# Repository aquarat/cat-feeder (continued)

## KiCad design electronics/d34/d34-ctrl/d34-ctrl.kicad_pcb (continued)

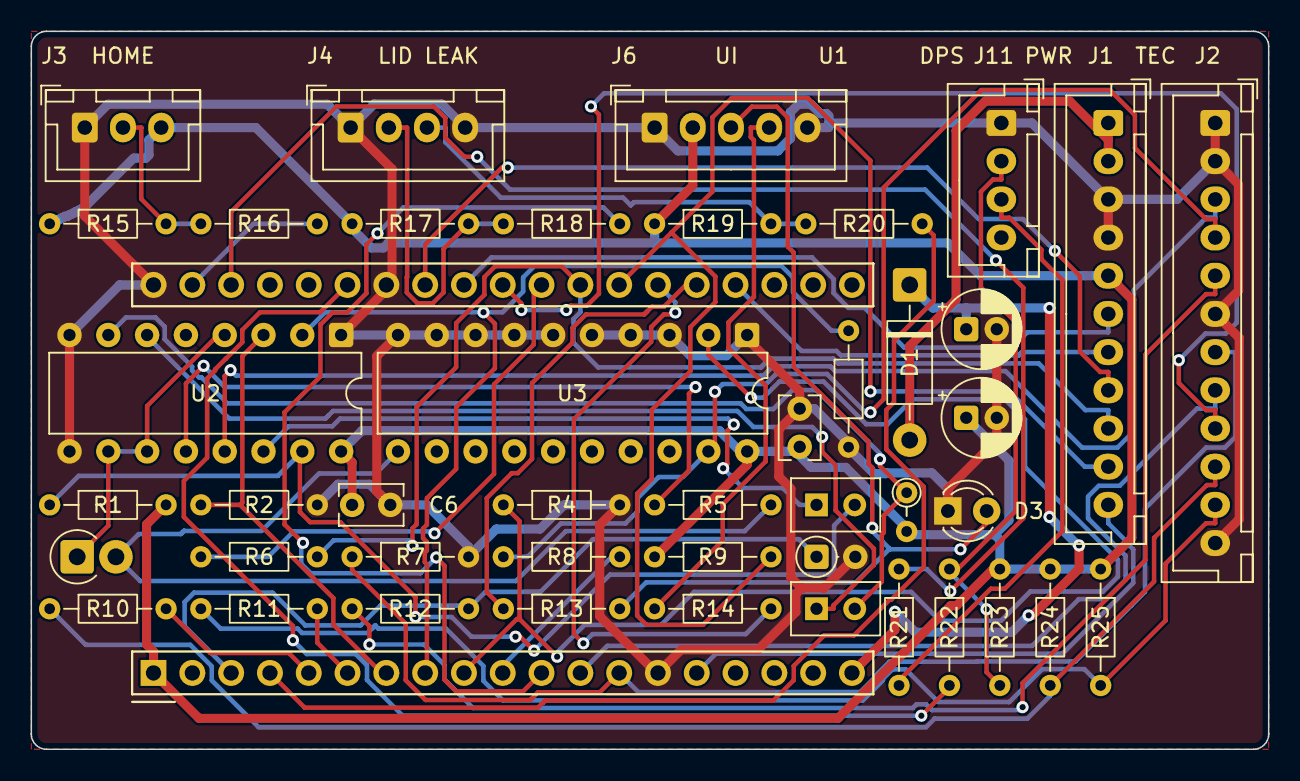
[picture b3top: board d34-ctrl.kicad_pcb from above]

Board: 2 copper layers, 81.0 x 47.0 mm, 45 parts (0 on the bottom side), 47 nets.

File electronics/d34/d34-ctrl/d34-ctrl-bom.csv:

Board,References,Qty,Value,Description,Manufacturer,MPN,KiCad footprint,Supplier,Stock no,Pack,Datasheet,Checked
d34-ctrl,U1,1,,"1x19 2.54 mm socket strip, 8.51 mm (2 per ESP32-DevKitC-32E)",Samtec,SSW-119-01-T-S,d34:ESP32-DevKitC-32E_Socket,RS,207-9240,1,samtec_ssw.pdf; esp32_devkitc_v4_dimensions.pdf,"verified: SSW body 8.51 high, 0.64 sq pins 3.68-6.35 deep; DevKitC rows 25.40, 48.26 x 27.94 + 6.04 antenna (Espressif drawing)"
d34-ctrl,D1 D2,2,,"Schottky 20 V 1 A, DO-41",onsemi,1N5817RLG,Diode_THT:D_DO-41_SOD81_P10.16mm_Horizontal,RS,625-4972,5,1n5817-19.pdf,"verified: VF max 0.32 V @ 0.1 A, 0.45 V @ 1 A; 20 V; DO-41 (onsemi p2)"
d34-ctrl,C1 C2,2,,"22 uF 50 V electrolytic, 5 x 11 mm",Rubycon,50YXF22M5X11,Capacitor_THT:CP_Radial_D5.0mm_P2.00mm,RS,224-4331,5,rubycon_yxf.pdf,"verified: 5 x 11 mm, 150 mA ripple (YXF p2); series marked obsolete by Rubycon but RS stock 1365 (2026-10-26); drop-in: Panasonic EEU-FR1H220 (FR p1, F 2.0 mm)"
d34-ctrl,D3,1,,3 mm green LED,Broadcom,HLMP-1503,LED_THT:LED_D3.0mm,RS,180-8502,10,hlmp-1503.pdf,"verified: D 3.17, H 6.35 max, leads 2.54 nominal, cathode = short lead, hole 0.98-1.08 (p1, p11)"
d34-ctrl,J1,1,,11-pin JST XH shrouded header,JST,B11B-XH-A(LF)(SN),Connector_JST:JST_XH_B11B-XH-A_1x11_P2.50mm_Vertical,RS,820-1535,10,jst_xh.pdf,"verified: eXH pitch 2.5, length 2.5(n-1)+4.9, h 7.0, hole 0.9-1.0, mated 9.8"
d34-ctrl,J2,1,,12-pin JST XH shrouded header,JST,B12B-XH-A(LF)(SN),Connector_JST:JST_XH_B12B-XH-A_1x12_P2.50mm_Vertical,RS,820-1539,10,jst_xh.pdf,"verified: eXH pitch 2.5, length 2.5(n-1)+4.9, h 7.0, hole 0.9-1.0, mated 9.8"
d34-ctrl,J11 J4,2,,4-pin JST XH shrouded header,JST,B4B-XH-A(LF)(SN),Connector_JST:JST_XH_B4B-XH-A_1x04_P2.50mm_Vertical,RS,820-1551,5,jst_xh.pdf,"verified: eXH pitch 2.5, length 2.5(n-1)+4.9, h 7.0, hole 0.9-1.0, mated 9.8"
d34-ctrl,U2,1,,"Dual retriggerable monostable, DIP-16 (TEC watchdog)",Toshiba,TC74HC123AP(F),Package_DIP:DIP-16_W7.62mm,RS,539-9456,5,tc74hc123ap.pdf,"verified: standard 74HC123 pinout, 2-6 V, tw ~= 1.0 Cx Rx (1 uF x 1 M ~ 1.0 s), Rx <= 1 M, DIP-16 4.15+-0.3 high (Toshiba JP sheet p1, p5-p10)"
d34-ctrl,U3,1,,"Octal transparent latch, DIP-20 (defrost-relay interlock)",Texas Instruments,SN74HC573AN,Package_DIP:DIP-20_W7.62mm,RS,217-5667,1,sn74hc573a.pdf,"verified: pinout p3, N20 rows 7.62, 5.08 max (p3, p31)"
d34-ctrl,R1 R26,2,,Resistor 470 k 1 % 0204 (74HC123 timing),Vishay,MBA02040C4703FRP00,Resistor_THT:R_Axial_DIN0204_L3.6mm_D1.6mm_P7.62mm_Horizontal,Farnell,4177865,10,,"Farnell listing: MBA 0204, 470 k, 1 %, 0.4 W (same 0204 body as MF0204; RS has no 470 k 0204 in small packs)"
d34-ctrl,R2 R4 R7 R15 R17 R20 R23 R24 R25,9,10k,"Resistor, metal film MF0204, 0.4 W, 1 %, axial",Yageo,MF0204FTE52-10K,Resistor_THT:R_Axial_DIN0204_L3.6mm_D1.6mm_P7.62mm_Horizontal,RS,199-7794,100,yageo_mf0.pdf,"verified: body 3.4+-0.3 x 1.9+-0.2 mm, lead 0.45 mm, M-forming P 6.0 mm (Yageo MF0 spec p3, p9)"
d34-ctrl,R3 R12 R19,3,47k,"Resistor, metal film MF0204, 0.4 W, 1 %, axial",Yageo,MF0204FTE52-47K,Resistor_THT:R_Axial_DIN0204_L3.6mm_D1.6mm_P7.62mm_Horizontal,RS,199-7828,100,yageo_mf0.pdf,"verified: body 3.4+-0.3 x 1.9+-0.2 mm, lead 0.45 mm, M-forming P 6.0 mm (Yageo MF0 spec p3, p9)"
d34-ctrl,C6 C7,2,100n,100 nF 50 V X7R radial MLCC,Murata,RDER71H104K0P1H03B,Capacitor_THT:C_Rect_L4.0mm_W2.5mm_P2.50mm,RS,190-2933,10,murata_rde.pdf,"verified: size 0 = 4.0 W x 2.5 T x 6.0 H mm, lead 0.5, P1 = 2.5 mm (RDE p2); h incl. coating allowance"
d34-ctrl,R5 R6 R8 R10 R11 R14 R16 R18 R21 R22,10,1k,"Resistor, metal film MF0204, 0.4 W, 1 %, axial",Yageo,MF0204FTE52-1K,Resistor_THT:R_Axial_DIN0204_L3.6mm_D1.6mm_P7.62mm_Horizontal,RS,199-7806,100,yageo_mf0.pdf,"verified: body 3.4+-0.3 x 1.9+-0.2 mm, lead 0.45 mm, M-forming P 6.0 mm (Yageo MF0 spec p3, p9)"
d34-ctrl,R9,1,4.7k,"Resistor, metal film MF0204, 0.4 W, 1 %, axial",Yageo,MF0204FTE52-4K7,Resistor_THT:R_Axial_DIN0204_L3.6mm_D1.6mm_P7.62mm_Horizontal,RS,199-7830,100,yageo_mf0.pdf,"verified: body 3.4+-0.3 x 1.9+-0.2 mm, lead 0.45 mm, M-forming P 6.0 mm (Yageo MF0 spec p3, p9)"
d34-ctrl,D9,1,,"Schottky clamp, DO-35 vertical (IO36 negative clamp)",STMicroelectronics,BAT42,Diode_THT:D_DO-35_SOD27_P2.54mm_Vertical_AnodeUp,RS,544-4758,5,bat42.pdf,"BAT42 small-signal Schottky 30 V, DO-35 (Vishay BAT42 sheet saved; ST part from RS): VF ~0.2-0.3 V at uA-mA"
d34-ctrl,R13,1,330,"Resistor, metal film MF0204, 0.4 W, 1 %, axial",Yageo,MF0204FTE52-330R,Resistor_THT:R_Axial_DIN0204_L3.6mm_D1.6mm_P7.62mm_Horizontal,RS,199-7821,100,yageo_mf0.pdf,"verified: body 3.4+-0.3 x 1.9+-0.2 mm, lead 0.45 mm, M-forming P 6.0 mm (Yageo MF0 spec p3, p9)"
d34-ctrl,C4 C5,2,1u,1 uF 50 V X7R radial MLCC,Murata,RDER71H105K2P1H03B,d34:C_Rect_L5.5mm_W3.2mm_P2.50mm,RS,190-2943,10,murata_rde.pdf,"verified: size 2 = 5.5 W x 3.15 T x 6.0 H mm, lead 0.5, P1 = 2.5 mm (RDE p2); custom footprint to that outline"
d34-ctrl,J3,1,,3-pin JST XH shrouded header,JST,B3B-XH-A(LF)(SN),Connector_JST:JST_XH_B3B-XH-A_1x03_P2.50mm_Vertical,RS,820-1557,5,jst_xh.pdf,"verified: eXH pitch 2.5, length 2.5(n-1)+4.9, h 7.0, hole 0.9-1.0, mated 9.8"
d34-ctrl,J6,1,,5-pin JST XH shrouded header,JST,B5B-XH-A(LF)(SN),Connector_JST:JST_XH_B5B-XH-A_1x05_P2.50mm_Vertical,RS,820-1560,5,jst_xh.pdf,"verified: eXH pitch 2.5, length 2.5(n-1)+4.9, h 7.0, hole 0.9-1.0, mated 9.8"
d34-ctrl,(off-board),1,,ESP32-DevKitC-32E module (plugs into U1 sockets); not stocked by RS/Farnell/CPC,Espressif,ESP32-DevKitC-32E,,Rapid Electronics,09-1099,,esp32_devkitc_v4_dimensions.pdf; esp32_devkitc_v4_sch.pdf,"verified: Espressif drawing + V4 schematic (5V pin after BAT760, AMS1117-3.3); DigiKey UK 1965-ESP32-DEVKITC-32E-ND GBP 7.47 is the alternative"
d34-ctrl,(off-board),1,,JST XH housing 3-way (home sensor lead),JST,XHP-3,,RS,820-1614,5,jst_xh.pdf,
d34-ctrl,(off-board),29,,"JST XH crimp contact SXH-001T-P0.6, AWG 28-22, for the three XH leads longer than any stocked pre-crimped lead: W01 ctrl-pwr link 335 mm (22), W28 lid reed 325 mm (2), W29 panel 300 mm (5); hand crimper Engineer PA-09",JST,SXH-001T-P0.6,,RS,123-5947,250,jst_xh.pdf,
d34-ctrl,(off-board),2,,JST XH housing 4-way (DPS5005 UART lead; lid reed + basin probe SENSE lead),JST,XHP-4,,RS,820-1618,5,jst_xh.pdf,
d34-ctrl,(off-board),1,,JST XH housing 5-way (panel LED/button lead),JST,XHP-5,,RS,820-1627,5,jst_xh.pdf,
d34-ctrl,(off-board),2,,"JST XH housing 11-way (ctrl-pwr link, both ends)",JST,XHP-11,,RS,820-1523,10,jst_xh.pdf,
d34-ctrl,(off-board),2,,"JST XH housing 12-way (ctrl-tec link, both ends)",JST,XHP-12,,RS,820-1532,10,jst_xh.pdf,
d34-ctrl,(off-board),26,,"JST XH pre-crimped lead, 300 mm 26 AWG, SXH contact both ends. W02 ctrl-tec link (12, both ends) and the single-ended leads W12, W30, W31, W33, W34 (14: each lead cut near ONE end, ~290 mm usable)",JST,01SXHSXH-26L300,,RS,820-1541,10,jst_xh.pdf,retailer data (RS/Farnell listing); contact = SXH-001T-P0.6 per eXH

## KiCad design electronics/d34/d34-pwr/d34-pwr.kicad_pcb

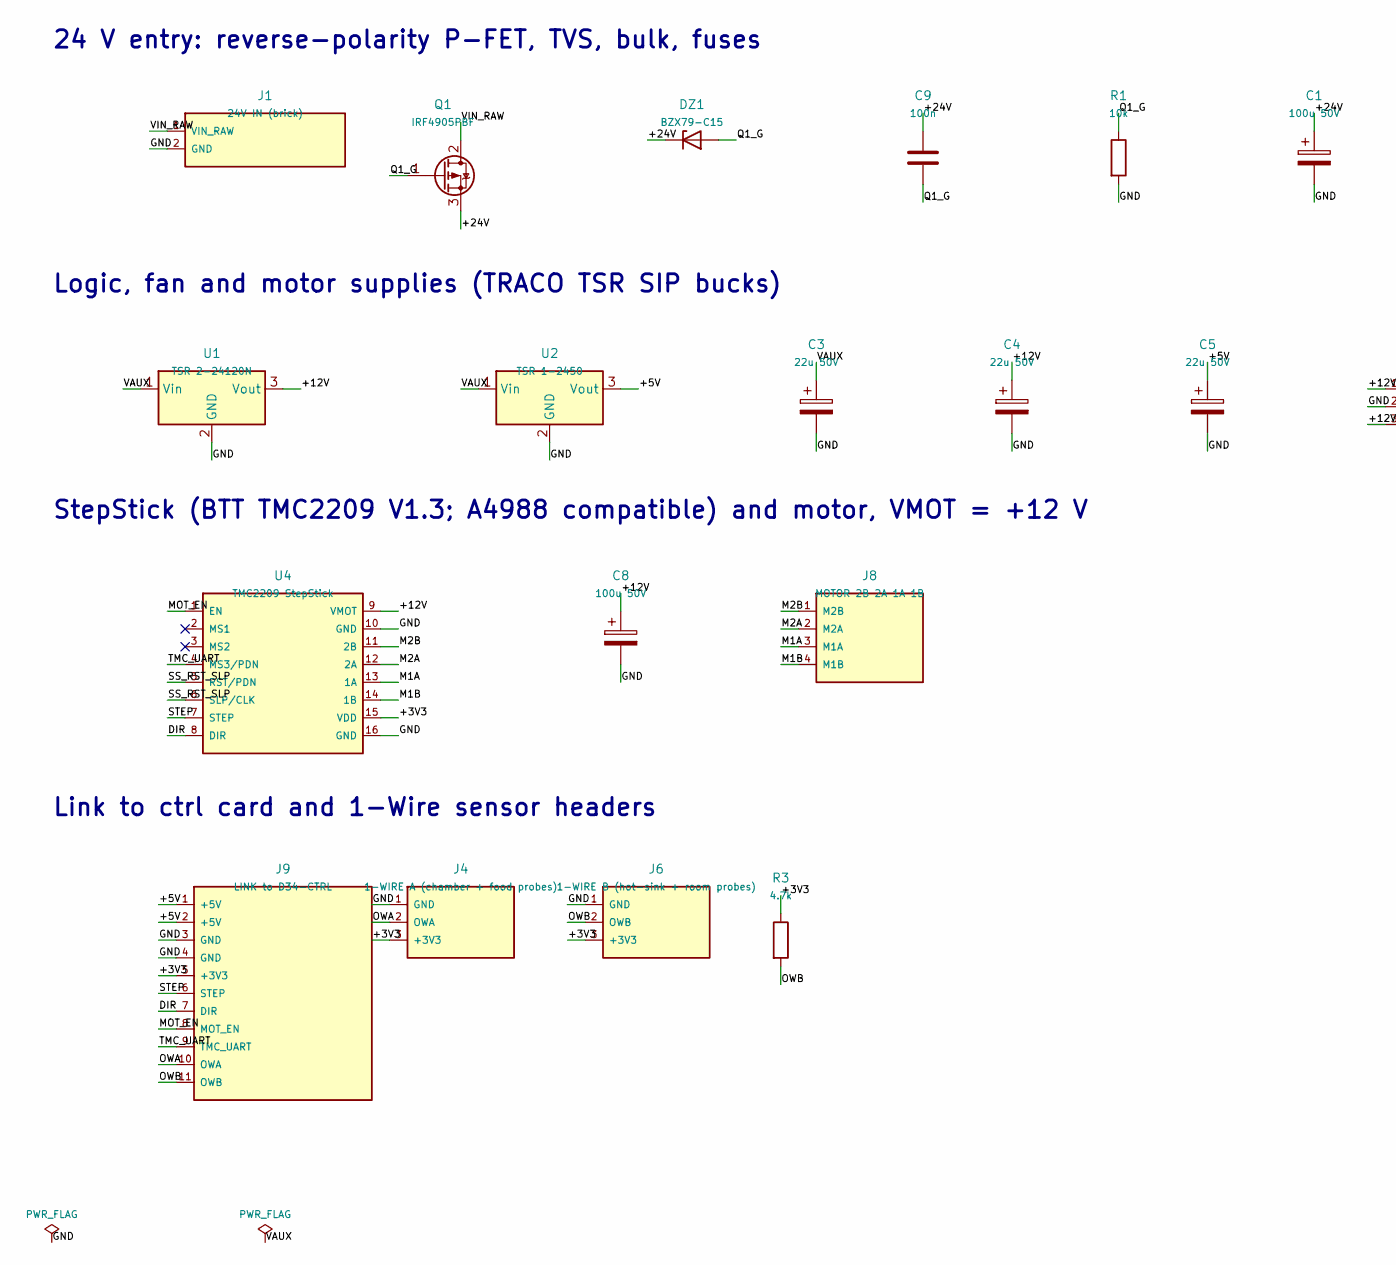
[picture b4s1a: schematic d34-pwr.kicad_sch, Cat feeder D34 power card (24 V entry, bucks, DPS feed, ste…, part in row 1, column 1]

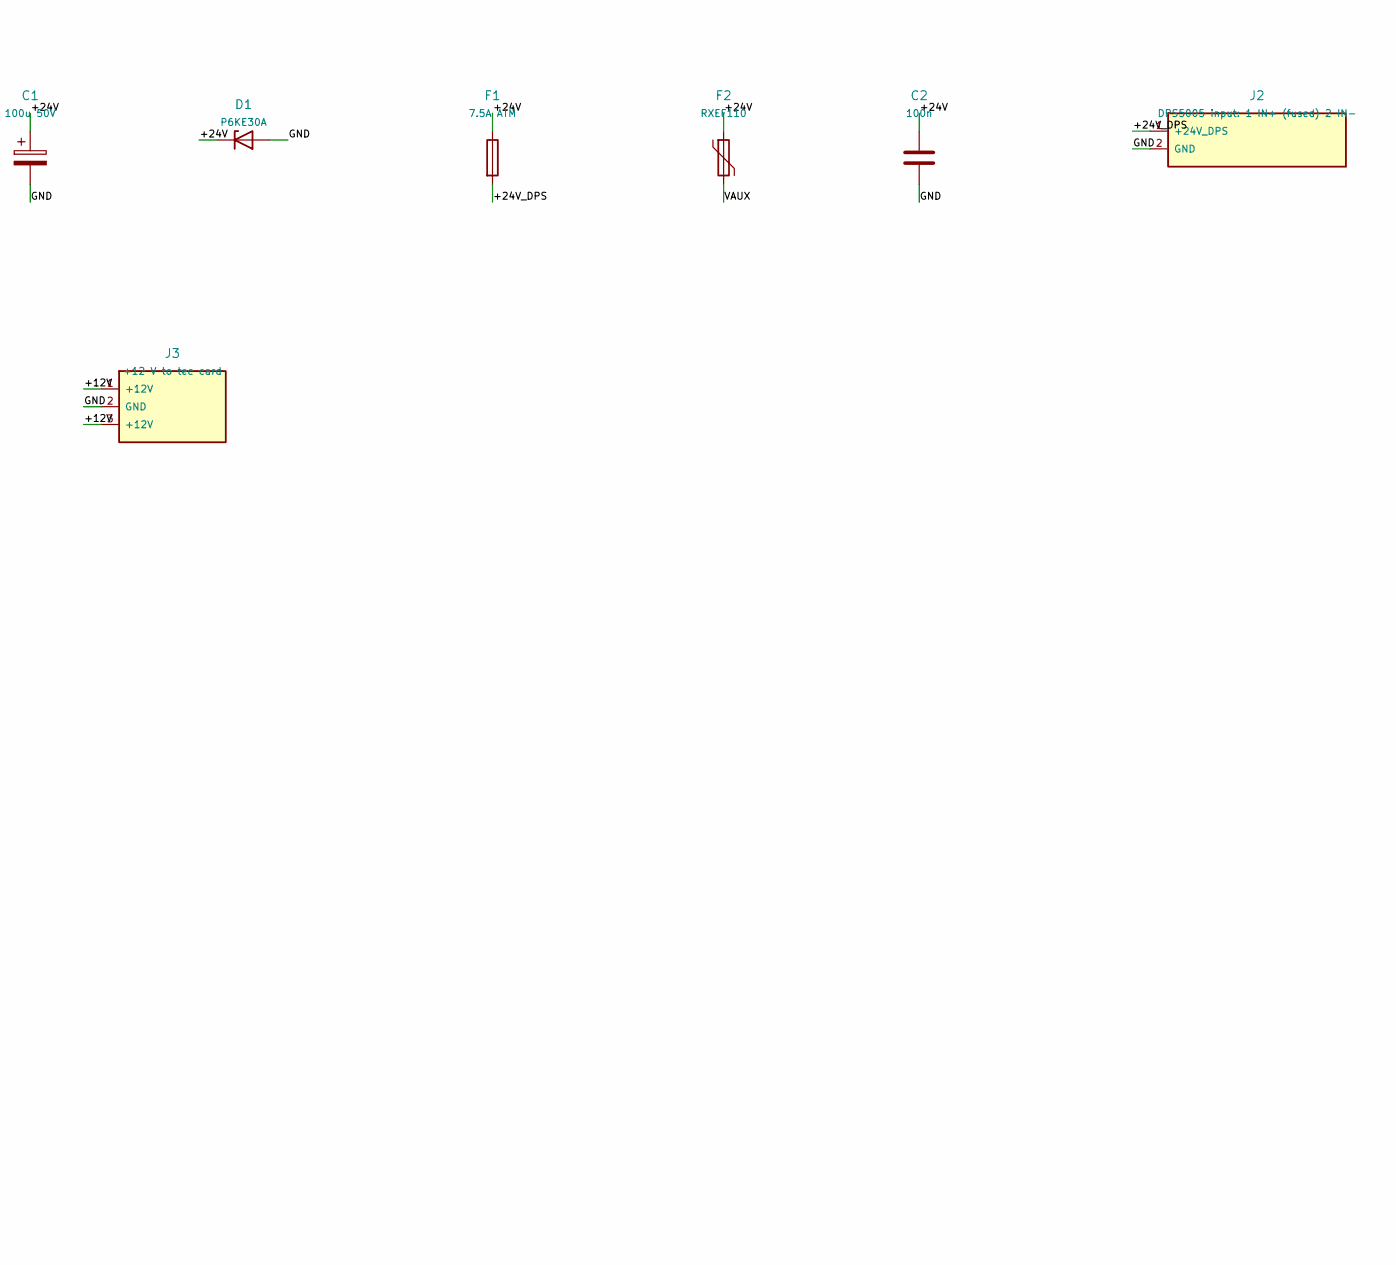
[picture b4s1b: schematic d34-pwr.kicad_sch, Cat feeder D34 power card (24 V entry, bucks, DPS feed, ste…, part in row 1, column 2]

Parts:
C1, C8: 100u 50V; CP_Radial_D8.0mm_P3.50mm; MPN EEU-FR1H101
C2, C9: 100n; C_Rect_L4.0mm_W2.5mm_P2.50mm; MPN RDER71H104K0P1H03B
C3, C4, C5: 22u 50V; CP_Radial_D5.0mm_P2.00mm; MPN 50YXF22M5X11
D1: P6KE30A; D_DO-15_P12.70mm_Horizontal; MPN P6KE30A
DZ1: BZX79-C15; D_DO-35_SOD27_P7.62mm_Horizontal; MPN BZX79-C15,133
F1: 7.5A ATM; Fuseholder_Blade_Mini_Keystone_3568; MPN 3568
F2: RXEF110; PTC_Radial_L13.0mm_W3.2mm_P5.08mm; MPN RXEF110
J1: 24V IN (brick); Molex_Mini-Fit_Jr_5566-02A_2x01_P4.20mm_Vertical; MPN 39-28-1023 (5566-02A)
J2: DPS5005 input: 1 IN+ (fused) 2 IN-; PhoenixContact_MSTBVA_2,5_2-G-5,08_1x02_P5.08mm_Vertical; MPN MSTBVA 2,5/2-G-5,08 (1755736)
J3: +12 V to tec card; JST_VH_B3P-VH_1x03_P3.96mm_Vertical; MPN B3P-VH(LF)(SN)
J4: 1-WIRE A (chamber + food probes); JST_XH_B3B-XH-A_1x03_P2.50mm_Vertical; MPN B3B-XH-A(LF)(SN)
J6: 1-WIRE B (hot-sink + room probes); JST_XH_B3B-XH-A_1x03_P2.50mm_Vertical; MPN B3B-XH-A(LF)(SN)
J8: MOTOR 2B 2A 1A 1B; JST_VH_B4P-VH_1x04_P3.96mm_Vertical; MPN B4P-VH(LF)(SN)
J9: LINK to D34-CTRL; JST_XH_B11B-XH-A_1x11_P2.50mm_Vertical; MPN B11B-XH-A(LF)(SN)
Q1: IRF4905PBF; TO-220-3_Vertical; MPN IRF4905PBF
R1: 10k; R_Axial_DIN0204_L3.6mm_D1.6mm_P7.62mm_Horizontal; MPN MF0204FTE52-10K
R3: 4.7k; R_Axial_DIN0204_L3.6mm_D1.6mm_P7.62mm_Horizontal; MPN MF0204FTE52-4K7
U1: TSR 2-24120N; Converter_DCDC_TRACO_TSR2-24xxN_TSR2-24xxxN_THT; MPN TSR 2-24120N
U2: TSR 1-2450; Converter_DCDC_TRACO_TSR-1_THT; MPN TSR 1-2450
U4: TMC2209 StepStick; StepStick_Socket_2x8_W12.70mm; MPN SSW-108-01-T-S

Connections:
/+3V3: J4.3 (+3V3), J6.3 (+3V3), J9.5 (+3V3), R3.1, U4.15 (VDD)
/+5V: C5.1, J9.1 (+5V), J9.2 (+5V), U2.3 (Vout)
/+12V: C4.1, C8.1, J3.1 (+12V), J3.3 (+12V), U1.3 (Vout), U4.9 (VMOT)
/+24V: C1.1, C2.1, C9.1, D1.1 (K), DZ1.1 (K), F1.1, F2.1, Q1.3 (S)
/+24V_DPS: F1.2, J2.1 (+24V_DPS)
/DIR: J9.7 (DIR), U4.8 (DIR)
/GND: C1.2, C2.2, C3.2, C4.2, C5.2, C8.2, D1.2 (A), J1.2 (GND), J2.2 (GND), J3.2 (GND), J4.1 (GND), J6.1 (GND), J9.3 (GND), J9.4 (GND), R1.2, U1.2 (GND), U2.2 (GND), U4.10 (GND), U4.16 (GND)
/M1A: J8.3 (M1A), U4.13 (1A)
/M1B: J8.4 (M1B), U4.14 (1B)
/M2A: J8.2 (M2A), U4.12 (2A)
/M2B: J8.1 (M2B), U4.11 (2B)
/MOT_EN: J9.8 (MOT_EN), U4.1 (EN)
/OWA: J4.2 (OWA), J9.10 (OWA)
/OWB: J6.2 (OWB), J9.11 (OWB), R3.2
/Q1_G: C9.2, DZ1.2 (A), Q1.1 (G), R1.1
/SS_RST_SLP: U4.5 (RST/PDN), U4.6 (SLP/CLK)
/STEP: J9.6 (STEP), U4.7 (STEP)
/TMC_UART: J9.9 (TMC_UART), U4.4 (MS3/PDN)
/VAUX: C3.1, F2.2, U1.1 (Vin), U2.1 (Vin)
/VIN_RAW: J1.1 (VIN_RAW), Q1.2 (D)

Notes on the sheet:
24 V entry: reverse-polarity P-FET, TVS, bulk, fuses
Logic, fan and motor supplies (TRACO TSR SIP bucks)
StepStick (BTT TMC2209 V1.3; A4988 compatible) and motor, VMOT = +12 V
Link to ctrl card and 1-Wire sensor headers

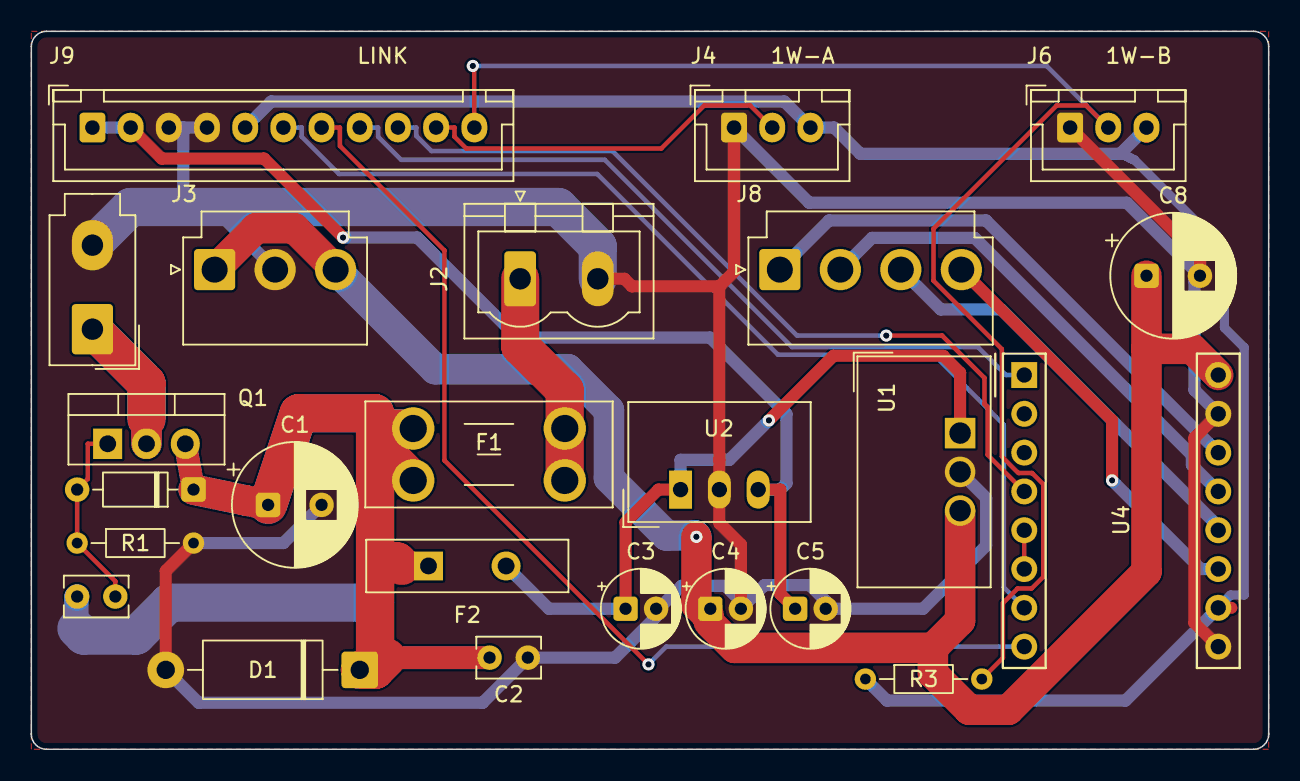
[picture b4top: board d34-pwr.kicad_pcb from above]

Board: 2 copper layers, 81.0 x 47.0 mm, 24 parts (0 on the bottom side), 20 nets.

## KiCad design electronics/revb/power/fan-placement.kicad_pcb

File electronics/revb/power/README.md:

# Rev B power-block handoff

**Selected:** AP63203WU-7 / C780769 for 3.3 V (1 A design budget); AP63201WU-7 / C2071044 for approximately 12 V (0.5 A fan-start budget, 0.14 A normal).

Read [rationale, layout constraints and qualification gaps](../../../kb/pcb-buck-integration.md).

- `circuit.json`: complete **22-component** numbered-pin integration contract, MPNs, JLC codes, KiCad symbols/footprints, datasheet links.
- `design.py`: source generator; follows the motor block's parts schema.
- `analysis.json`, `analyze.py`, `test_power.py`: explicit assumptions and eight analytical/fault-injection tests.
- `stock-evidence.json`, `refresh-stock.py`: read-only public stock snapshots, including rejected candidates; selection is defined by `circuit.json`, not by presence in the evidence file.
- `kicad-audit.json`, `audit_kicad.py`, `power.pretty/`: installed KiCad 9.0.2 symbol/pad checks and exact standard footprint copies.
- `reference-sources.json`, retained PDFs/text: manufacturer-authored reference evidence and mirror provenance.

**Required upstream contract:** `SYS_20V` is a hardware-qualified 20 V switched supply, OFF for fallback contracts and contract loss. Both buck EN pins tie to this supply. Neither rail waits on ESP32 firmware. Feed motor power and DPS5005 separately from the qualified 20 V bus; include the buck banks' 40 µF nominal input capacitance in upstream switch inrush calculations.

The new PCB integrator must check layout/loop/transient/thermal behavior. These files contain no full-board layout and no physical test results. Capacitor DC-bias retention and 10 µs load-step recovery are screening assumptions, not measured guarantees. The 0.5 A fan-start budget is not a qualified continuous thermal rating.

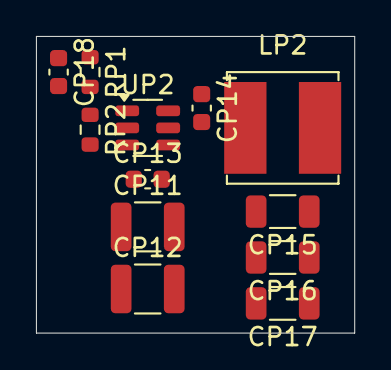
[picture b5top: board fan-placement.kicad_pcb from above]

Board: 2 copper layers, 17.7 x 16.5 mm, 12 parts (0 on the bottom side), 6 nets, no tracks yet.

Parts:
CP11, CP12: 10u 50V X7R; C_1210_3225Metric
CP13, CP14: 100n 50V X7R; C_0603_1608Metric
CP15, CP16, CP17: 22u 25V X5R; C_1206_3216Metric
CP18: 56p 50V C0G; C_0603_1608Metric
LP2: 10uH; L_Bourns_SRN6045TA
RP1: 249k 1%; R_0603_1608Metric
RP2: 18k 1%; R_0603_1608Metric
UP2: AP63201WU-7; TSOT-23-6

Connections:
+12V: CP15.1, CP16.1, CP17.1, CP18.1, LP2.2, RP1.1
GND: CP11.2, CP12.2, CP13.2, CP15.2, CP16.2, CP17.2, RP2.2, UP2.4
PWR_BST2: CP14.1, UP2.6
PWR_FB12: CP18.2, RP1.2, RP2.1, UP2.1
PWR_SW2: CP14.2, LP2.1, UP2.5
SYS_20V: CP11.1, CP12.1, CP13.1, UP2.2, UP2.3

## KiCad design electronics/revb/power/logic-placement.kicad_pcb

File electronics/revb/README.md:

# Controller revision B — integrated power and motion

**In development.** The owner requested integrating USB-C PD, the stepper
driver and the logic/fan regulators onto the main PCB. This revision is a new
design, not the independently reviewed revision A saved in the supplier project.

## Intended electrical architecture

```text
USB-C, 20 V / 5 A capable source and e-marked cable
  └─ STUSB4500 negotiation, protection and controlled power path
       ├─ efficient 3.3 V supply → ESP32, sensors and interface logic
       ├─ efficient 12 V supply → four-wire fan
       ├─ onboard current-regulating A4988 → bipolar stepper
       └─ DC power output → external DPS5005 → TEC array
```

The PD breakout, plug-in motor carrier and separate logic/fan buck modules are
replaced by assembler-fitted components. The DPS5005 remains a separate TEC
regulator. A 100 W input contract is a total-source budget, not 100 W available
to the TECs after auxiliaries and conversion losses.

Functional circuit selection, component stock/footprint checks and JLCPCB
design-rule research are being developed in `pd/`, `motor/`, `power/` and `dfm/`.
The generator emits an editable KiCad schematic and explicitly **unrouted**
placement; those alone are not manufacturing deliverables. Routing, DRC,
electrical review, populated enclosure clearance and supplier-process checks
must refer to this revision's actual artifacts.

## Version identification

`version.py` computes a full SHA-256 digest of the explicitly listed circuit,
footprint and layout sources. The PCB silkscreen and schematic title carry:

- `Rev B / <12-character Git hash>` for committed, unchanged design sources;
- the same with `-dirty` when those sources differ or are untracked;
- `Rev B / src-<12-character source hash>` before the first Git commit.

`version.json` records the full commit, source digest and individual source
hashes. Generated PCB/Gerber/BOM files are hashed separately after export;
feeding them into their own printed identifier would create a circular hash.
The Git identifier is the latest commit touching the listed design sources;
committing only generated artifacts therefore does not force another identifier.
The current repository has no commits, so its initial identifier uses the
source hash. No commit or supplier upload is implicit in generating a version.

Revision A's frozen files and simulation results remain under `../pcb/` and
`../sim/`. Their numerical checks do not qualify the changed revision B circuit.

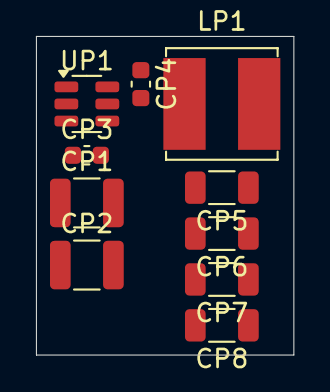
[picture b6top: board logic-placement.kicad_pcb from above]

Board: 2 copper layers, 14.3 x 17.7 mm, 10 parts (0 on the bottom side), 5 nets, no tracks yet.

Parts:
CP1, CP2: 10u 50V X7R; C_1210_3225Metric
CP3, CP4: 100n 50V X7R; C_0603_1608Metric
CP5, CP6, CP7, CP8: 22u 25V X5R; C_1206_3216Metric
LP1: 6.8uH; L_Bourns_SRN6045TA
UP1: AP63203WU-7; TSOT-23-6

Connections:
+3V3: CP5.1, CP6.1, CP7.1, CP8.1, LP1.2, UP1.1
GND: CP1.2, CP2.2, CP3.2, CP5.2, CP6.2, CP7.2, CP8.2, UP1.4
PWR_BST1: CP4.1, UP1.6
PWR_SW1: CP4.2, LP1.1, UP1.5
SYS_20V: CP1.1, CP2.1, CP3.1, UP1.2, UP1.3

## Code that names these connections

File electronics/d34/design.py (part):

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# signals whose boot level is safe: IO0 button (pull-up on DevKit), IO2 LED
# (pull-down via LED), IO12 fan PWM with 10k pull-down (3.3 V flash), IO5 fan PWM,
# IO15 DIR (no external pull). TEC_EN/WDT_KICK use IO32/IO33, quiet at reset.
GPIO = {'3V3': '+3V3', 'EN': None, 'IO36': 'THERMO_OK_IN', 'IO39': 'LEAK_IN', 'IO34': 'TACH1_IN', 'IO35': 'TACH2_IN',
        'IO32': 'TEC_EN', 'IO33': 'WDT_KICK', 'IO25': 'DEFROST_REQ', 'IO26': 'DEFROST_FB', 'IO27': 'LID_IN',
        'IO14': 'FAN2_PWM', 'IO12': 'FAN1_PWM', 'GND': 'GND', 'IO13': 'OWB', 'SD2': None, 'SD3': None,
        'CMD': None, '5V': '+5V_DK',
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    B.conn('J1', 'XH11', 'LINK to D34-PWR', LINK_PWR, 70.5, 6.0, 270, label='LINK-PWR', ref_at=(70.0, 1.6, 0))
    B.conn('J2', 'XH12', 'LINK to D34-TEC', LINK_TEC, 77.5, 6.0, 270, label='LINK-TEC', ref_at=(77.0, 1.6, 0))
    B.conn('J11', 'XH4', 'DPS5005 UART (3.3 V TTL; DPS order GND TX RX 3V3)',
           [('GND', 'GND'), ('DPS_TXD', 'LOGIC'), ('DPS_RXD', 'LOGIC'), (None, 'NC')], 63.5, 6.0, 270, label='DPS', ref_at=(63.0, 1.6, 0))
    # ---------------------------------------------------------- safety logic (under the DevKit)
    B.group = 'TEC watchdog (74HC123) and defrost interlock latch (74HC573)'
    # Both DIPs are turned 270 deg so VCC (pin 16 / pin 20) sits at the bottom-right corner, next to its
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          note='holds LE low (<= 0.4 V) whenever 1Q-bar is low, i.e. while K1 is commanded on')
    B.add('R26', 'R470V', '470k', {1: 'LD_RC', 2: '+3V3'}, 57.3, 30.2, 270, ref_at='hide', note='latch-delay timing (74HC123 half 2)')
    ur('R6', '1k', 'TMC_TX_G', 'TMC_UART', 1, 1, note='TMC2209 single-wire UART: TX via 1k, RX (IO16) direct')
    ur('R7', '10k', 'FAN1_PWM', 'GND', 2, 1, note='GPIO12 strap must read low at boot (3.3 V flash)')
    ur('R8', '1k', 'K2_ON', 'DEFROST_FB', 3, 1, note='latched K2 state read back on IO26')
    ur('R9', '4.7k', '+3V3', 'OWA', 4, 1, note='1-Wire bus A pull-up (bus B pull-up is on the pwr card)')
    ur('R10', '1k', 'TACH1', 'TACH1_IN', 0, 2)
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    s3 = [('GND', 'GND'), ('HOME', 'LOGIC'), ('+3V3', '3V3')]
    # Harness-access pass (2026-10-26): three plugs instead of four, spread to ~7 mm gaps. The lid reed and the
    # basin-full probe arrive on two cables that terminate in the same XHP-4 housing (J4 = GND, LID, LEAK, GND).
    B.conn('J3', 'XH3', 'HOME sensor (DRV5023 hall, 3.3 V, open drain)', s3, 3.5, 6.3, 0, label='HOME', ref_at=(1.5, 1.6, 0))
    B.conn('J4', 'XH4', 'LID reed + basin-full probe', [('GND', 'GND'), ('LID', 'LOGIC'), ('LEAK', 'ANALOG'), ('GND', 'GND')],
           20.9, 6.3, 0, label='SENSE', ref_at=(18.9, 1.6, 0))
    B.conn('J6', 'XH5', 'UI: panel LED + button', [('GND', 'GND'), ('+3V3', '3V3'), ('LED_EXT', 'LOGIC'), ('BTN', 'LOGIC'), ('GND', 'GND')],
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                    'Motor': dict(width=0.8, clearance=0.3, nets=['M1A', 'M1B', 'M2A', 'M2B'])}
    B.solid_pads = set(HC)
    B.group = '24 V entry: reverse-polarity P-FET, TVS, bulk, fuses'
    # J1 is turned 180 deg (pin 1 = +24 V at the bottom) so VIN_RAW runs 8 mm to the FET drain on both
    # layers without crossing the brick return; GND leaves upwards and runs above the VH/MSTB row.
    B.conn('J1', 'MF2', '24V IN (brick)', [('VIN_RAW', '24V'), ('GND', 'GND')], 4.0, 19.5, 180, label='24V IN', ref_at='hide')
    B.add('Q1', 'IRF4905', 'IRF4905PBF', {1: 'Q1_G', 2: 'VIN_RAW', 3: '+24V'}, 5.0, 27.0, 0, ref_at=(14.5, 24.0, 0),
          note='conducts only with correct input polarity; gate clamped to -15 V')
    B.add('DZ1', 'DZ15S', 'BZX79-C15', {1: '+24V', 2: 'Q1_G'}, 10.62, 30.0, 180, ref_at='hide')
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    B.add('F3', 'PTC050', 'RXEF050', {1: '+12V', 2: 'FAN3_12'}, 61.2, 20.0, 0, ref_at='hide', note='FAN3 (spare) feed')
    B.add('Q4', 'IRLZ44N', 'IRLZ44N', {1: 'FAN2_PWM', 2: 'FAN2_N', 3: 'GND'}, 62.0, 26.9, 0, ref_at='hide', note='FAN2 low side')
    B.add('Q5', 'IRLZ44N', 'IRLZ44N', {1: 'FAN3_PWM', 2: 'FAN3_N', 3: 'GND'}, 72.7, 26.9, 0, ref_at='hide', note='FAN3 low side')
    B.conn('J5', 'FAN4', 'FAN1 12 V 4-pin PWM (NF-A12x25)', [('GND', 'GND'), ('FAN1_12', '12V'), ('TACH1', 'LOGIC'), ('FAN1_OD', 'LOGIC')],
           37.0, 6.4, 0, label='FAN1', ref_at=(35.0, 1.6, 0))
    B.conn('J6', 'FAN4', 'FAN2 12 V blower (switched DC low side), tach', [('FAN2_N', 'FANGND'), ('FAN2_12', '12V'), ('TACH2', 'LOGIC'), (None, 'NC')],
           48.5, 6.4, 0, label='FAN2', ref_at=(46.5, 1.6, 0))
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
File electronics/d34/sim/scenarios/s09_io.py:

"""S09 - Sensor and I/O interfaces (ngspice, full system powered).

1-Wire rise time on both buses with all probe leads at maximum length; lid / home / leak input levels through
their series resistors and leads; ESD into a lid lead (HBM and IEC 61000-4-2 contact) vs the ESP32 pin clamps;
ESP32 strapping pin levels at reset; THERMO_OK and DEFROST_FB logic levels.
"""
import numpy as np

from d34sim import common, flows, report
from d34sim import models as M_
from d34sim.circuit import Ctx
from d34sim.netlist import spice_node

TITLE = '1-Wire timing, digital input levels, ESD into leads, ESP32 strapping pins'


def run(env):
    chk = report.Checks('s09_io', env.outdir('s09_io'))
    L = env.limit
    N, R = flows.names(env)
    ctrl = env.cards['ctrl']
    dk = R['devkit']
    io = {ctrl.pin_func[(dk, p)]: net for p, net in ctrl.pins(dk).items()}
    nio = lambda gpio: spice_node('ctrl', io[gpio]).lower()
    vdd = 3.3
    vih, s_vih = L('esp32_vih_frac')
    vil, s_vil = L('esp32_vil_frac')
    # ------------------------------------------------------------------ 1-Wire
    ow_leads = [k for k, v in env.harness['leads'].items() if v['b'] == 'ext:ds18b20' and env.cards['pwr'].pins(v['a'][1])]
    onewire = {k: dict(pull='DC 0', c_in=25e-12) for k in ow_leads}
    first = {}
    for k in ow_leads:   # one sensor per bus pulls low 100-110 us, then releases
        net = env.cards['pwr'].net(env.harness['leads'][k]['a'][1], '2')
        if net not in first:
            first[net] = k
            onewire[k]['pull'] = 'PWL(0 0 100u 0 100.02u 1 110u 1 110.02u 0)'
    rows = []
    for corner in ('nom', 'max'):
        def make(nv):
            ctx = Ctx(dict(temp_C=40.0, length=corner, C=corner), no_vendor=nv)
            return common.build(env, ctx, brick=dict(v=24.0, t_close=None), onewire=onewire)
        bus_gpio = {net: [g for g, n in io.items() if n == net] for net in first}
        vecs = [f'v({nio(g[0])})' for g in bus_gpio.values() if g]
        c, info, r = common.run_robust(make, f's09_ow_{corner}', vecs, 'tran 20n 140u 0 50n', chk)
        t = r['time']
        for (net, g), v in zip(bus_gpio.items(), vecs):
            t_ds = common.first_cross(t, r[v], L('ds18b20_vih')[0], after=110e-6) - 110e-6
            t_esp = common.first_cross(t, r[v], vih * vdd, after=110e-6) - 110e-6
            vol = r[v][(t > 105e-6) & (t < 109e-6)].mean()
            rows.append(dict(bus=net, gpio=g[0], corner=corner, rise_to_ds_vih_us=t_ds * 1e6, rise_to_esp_vih_us=t_esp * 1e6, vol=vol,
                             probes=sum(env.harness['leads'][k].get('probes', 1) for k in ow_leads
                                        if env.cards['pwr'].net(env.harness['leads'][k]['a'][1], '2') == net)))
    chk.csv('onewire.csv', rows)
    w = max(rows, key=lambda x: x['rise_to_esp_vih_us'])
    s_t = L('onewire_sample_us')
    chk.add('ow_rise', '1-Wire release to ESP32 VIH (0.75 VDD), worst bus, all probe leads 0.5 m', w['rise_to_esp_vih_us'], s_t[0] - 2.0, '<=', 'us',
            f'{s_t[1]}; master releases ~2 us after slot start', corner=f"{w['bus']} ({w['probes']} probes, lead {w['corner']})", severity='functional')
    w = max(rows, key=lambda x: x['vol'])
    chk.add('ow_vol', '1-Wire low level while a DS18B20 pulls down (vs ESP32 VIL)', w['vol'], vil * vdd, '<=', 'V', s_vil, severity='functional')
    # ------------------------------------------------------------------ inputs, strapping, status levels (DC)
    def make_dc(nv):
        ctx = Ctx(dict(temp_C=40.0), no_vendor=nv, boot_pulls=True)
        leads = [k for k in ('LID', 'HOME', 'LEAK') if k in env.harness['leads']]
        c, info = common.build(env, ctx, brick=dict(v=24.0, t_close=None), extra_leads=leads)
        lid, home, leak = (info[k][0] if k in info else {} for k in ('LID', 'HOME', 'LEAK'))
        c.add('* lid switch closed (0.1 ohm + lead), home sensor open collector on (VOL ~0.2 V @ 0.33 mA), leak probe 47 kohm (wet)')
        if lid:
            c.add(f'Rlid {lid["1"]} {lid["2"]} 0.1')
        if home:
            c.add(f'Rhome {home["2"]} home_x 400', f'Vhome home_x {home["1"]} 0.07')
        if leak:
            c.add(f'Rleak {leak["1"]} {leak["2"]} 47k')
        elif lid and '3' in lid and '4' in lid:   # D34-2: basin-full probe shares the lid XH-4 (pins 3/4)
            c.add(f'Rleak {lid["3"]} {lid["4"]} 47k')
        return c, info
    want = ['IO27', 'IO23', 'IO39', 'IO0', 'IO2', 'IO12', 'IO15', 'IO5', 'IO36', 'IO26']
    vecs = [f'v({nio(g)})' for g in want if g in io] + [f'v({N["v3v3"]})']
    c, info, r = common.run_robust(make_dc, 's09_dc', vecs, 'tran 1u 2m 0 10u', chk)
    V = {g: float(r[f'v({nio(g)})'][-1]) for g in want if g in io}
    v33 = float(r[f'v({N["v3v3"]})'][-1])
    chk.add('lid_closed', f'Lid switch closed: level at the ESP32 pin ({io.get("IO27")})', V.get('IO27', np.nan), vil * v33, '<=', 'V', s_vil)
    chk.add('home_on', 'Home sensor active (open collector 0.2 V): level at the ESP32 pin', V.get('IO23', np.nan), vil * v33, '<=', 'V', s_vil)
    chk.add('strap_io12', 'Strapping: GPIO12 (MTDI) at reset must read 0 for 3.3 V flash (WROOM-32E)', V.get('IO12', np.nan), vil * v33, '<=', 'V',
            'ESP32 datasheet strapping: MTDI = 0 -> VDD_SDIO 3.3 V; ' + s_vil, severity='functional')
    chk.add('strap_io0', 'Strapping: GPIO0 at reset reads 1 (SPI boot) with the panel button released', V.get('IO0', np.nan), vih * v33, '>=', 'V',
            s_vih, severity='functional')
    chk.note('Strap levels at reset: ' + ', '.join(f'{g} {V[g]:.2f} V' for g in ('IO0', 'IO2', 'IO5', 'IO12', 'IO15') if g in V) +
             '. GPIO5/GPIO15 only set SDIO timing / boot-log; GPIO2 is don\'t-care when GPIO0 = 1.')
    leak_net = io.get('IO39')
    rpu = [M_.parse_value(ctrl.comps[r]['value']) for r in ctrl.comps if r.startswith('R')
           for nets in [set(ctrl.pins(r).values())] if 'LEAK' in nets and N['v3v3'] and any(x.upper() == '+3V3' for x in nets)]
    rpu = rpu[0] if rpu else 100e3
    leak_rows = [dict(probe_ohm=rp, adc_V=3.3 * rp / (rpu + rp), pullup_ohm=rpu) for rp in (1e3, 10e3, 47e3, 100e3, 470e3, 1e6, 1e9)]
    chk.csv('leak_divider.csv', leak_rows)
    chk.note(f"Basin-full probe (ADC, {rpu / 1e3:.0f} k pull-up): 47 k wet -> {V.get('IO39', float('nan')):.2f} V simulated; dry -> 3.3 V. "
             'Divider table in leak_divider.csv.')
    # ------------------------------------------------------------------ ESD into an input lead (analytic)
    # A discharge into a lead reaches the ESP32 pin through the 1 k series resistor and the pin's clamp diodes; with no
    # TVS the peak pin current is bounded by V_esd / (R_gun + R_series). (A SPICE transient was not used: the pin
    # clamp and rail impedances of the ESP32 at ns time scales are not modelled credibly.)
    r_ser = [M_.parse_value(ctrl.comps[x]['value']) for x in ctrl.comps
             if x.startswith('R') and io.get('IO27') in ctrl.pins(x).values() and 'LID' in ctrl.pins(x).values()]
    r_ser = r_ser[0] if r_ser else 1e3
    esd_rows = []
    for name, (vesd, cesd, resd) in {'HBM 2 kV': (2000, 100e-12, 1500), 'IEC 61000-4-2 2 kV contact': (2000, 150e-12, 330),
                                     'IEC 61000-4-2 8 kV contact': (8000, 150e-12, 330)}.items():
        esd_rows.append(dict(event=name, i_pin_pk_est=vesd / (resd + r_ser), r_series=r_ser))
    chk.csv('esd.csv', esd_rows)
    lim, s = L('esp32_hbm_pin_current')
    hbm = esd_rows[0]
    chk.add('esd_hbm', 'HBM 2 kV on a lid lead: peak current into the ESP32 pin clamp (through the 1 k series resistor)', hbm['i_pin_pk_est'], lim, '<=',
            'A', s, severity='rating', detail='analytic bound V/(R_gun + R_series)')
    for row in esd_rows[1:]:
        chk.add(f"esd_iec_{row['event'].split()[-3]}", f"{row['event']} on a lid lead: peak current into the ESP32 pin clamp", row['i_pin_pk_est'], lim, '<=', 'A',
                s + '; no TVS on the inputs', severity='rating', advisory=True,
                detail='leads are inside the enclosure; exposure is only during servicing. Add a TVS array (e.g. per-input 5 V TVS) if leads are touchable')
    # ------------------------------------------------------------------ status levels
    th = V.get('IO36', np.nan)
    chk.add('thermo_ok_level', 'THERMO_OK (thermostats closed) at the ESP32 input vs VIH (digital read)', th, vih * v33, '>=', 'V', s_vih,
            severity='functional', detail='margin is small; reading IO36 with the ADC (threshold ~1.4 V) avoids it (see S11 Monte Carlo)')
    return chk

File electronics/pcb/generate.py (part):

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# Espressif module pin numbers, not bare-chip pad numbers.
add('U1','ESP32-WROOM-32E-N4','RF_Module:ESP32-WROOM-32E','RF_Module:ESP32-WROOM-32E',{
 1:'GND',2:'+3V3',3:'EN',6:'FAN_TACH',7:'BUS_SENSE',8:'INDEX',9:'HOME',
 10:'TEC_EN',11:'FAN_PWM_GPIO',12:'ONEWIRE',15:'GND',16:'UART_OEn',
 25:'BOOT',27:'DPS_RX',28:'DPS_TX',30:'STEP',31:'DIR',33:'I2C_SDA',
 34:'U0RX',35:'U0TX',36:'I2C_SCL',37:'MOTOR_RUN',38:'GND',39:'GND'},
 (75,63,0),'C701341')
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resistor(5,'10k','+3V3','HOME',63,83)
resistor(6,'10k','+3V3','TACH_EXT',88,73)
resistor(7,'1k','TACH_EXT','FAN_TACH',88,69)
resistor(8,'4.7k','FAN_PWM_GPIO','FAN_BASE',87,83)
resistor(9,'100k','FAN_BASE','GND',82,83)
resistor(10,'10k','TEC_EN','GND',88,110)
resistor(11,'10k','MOTOR_RUN','GND',69,83)
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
